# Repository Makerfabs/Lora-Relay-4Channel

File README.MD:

Lora-Relay-4Channel
 ==
Introduce
-
4-Channel Lora Relay-10A based on the Arduino, users can program it with Arduino IDE, which is very easy especially suit for the none-programmers. There are also guide for users to learn how to create the first IoT project with this board, with which the starters can learn the hardware and programming skill quickly. <br>
[Makerfabs Wiki](https://makerfabs.com/wiki/index.php?title=Main_Page) <br>
<br/>

Feature
-
* ATMEL Atmega328P: High Performance, Low Power Atmel®AVR® 8-Bit Microcontroller
* Speed Grade:20Mhz
* Flash:32Kbytes
* RAM: 2KBytes
* EEPROM: 1Kbytes
* Relay type: General Purpose 
* Rated current of relay contact: 10A
* Coil type of relay: Non Latching
* Coil voltage of relay: 5V
* Switching voltage of relay: (277VAC , 28VDC) Max
* DC12V or 5V input

Usage
-
 ### Hardware connection
The USB TO UART TOOL is needed to connect the module and PC. <br>
The pins connections is: 
|4-Channel Lora Relay-10A |USB-to-UART Tool |
|---|---|
|3V3 |3V3 |
|GND |GND |
|RX |TXD |
|TX |RXD |

 ### Software setup
Open the Arduino, select the tools menu and set the parameter, as the figure:<br>

 ### Lora Transmitter
Prepare a Lora receiver and put it aside.<br>
Open the code "LoraTransmitter/LoraTransmitter.ino" and modify the frequency macro according to your board is 433Mhz or 868Mhz or 915Mhz. <br>
```
#define RF95_FREQ 868.0  
```
Verify and upload it. <br>
  <br>
Open the “Tools—Serial Monitor” and the information of Lora Transmitter will be shown in the monitor, as the picture. 

 ### Lora receiver
Open the "LoraReceiver/LoraReceiver.ino" and modify the frequency macro according to your board is 433Mhz or 868Mhz or 915Mhz. 
```
#define RF95_FREQ 868.0 
```
Verify and upload it. After finish, open the “Tools—Serial Monitor”, If have a transmitter next to it, the receive will receive data sent by the Transmitter and the monitor will show the received information in the window, as the picture.
  <br>
If the receiver has received it, the relay will be turned on or turned off. Light on when COM connect to NO, light off when COM connect to NC and Normally light off.<br>
 <br>
Control relay pins: <br>
|Atmega328P	|Relay |
|---|---|
|D4	|K1 |
|D3	|K2 |
|A3	|K3 |
|A2	|K4 |

The following table lists all of the relay's pins and their functionality.<br>
|Pin	|Description | 
|---|---|
|NC	Normally |Closed | 
|NO	Normally |Opened | 
|COM	|Switch Common |

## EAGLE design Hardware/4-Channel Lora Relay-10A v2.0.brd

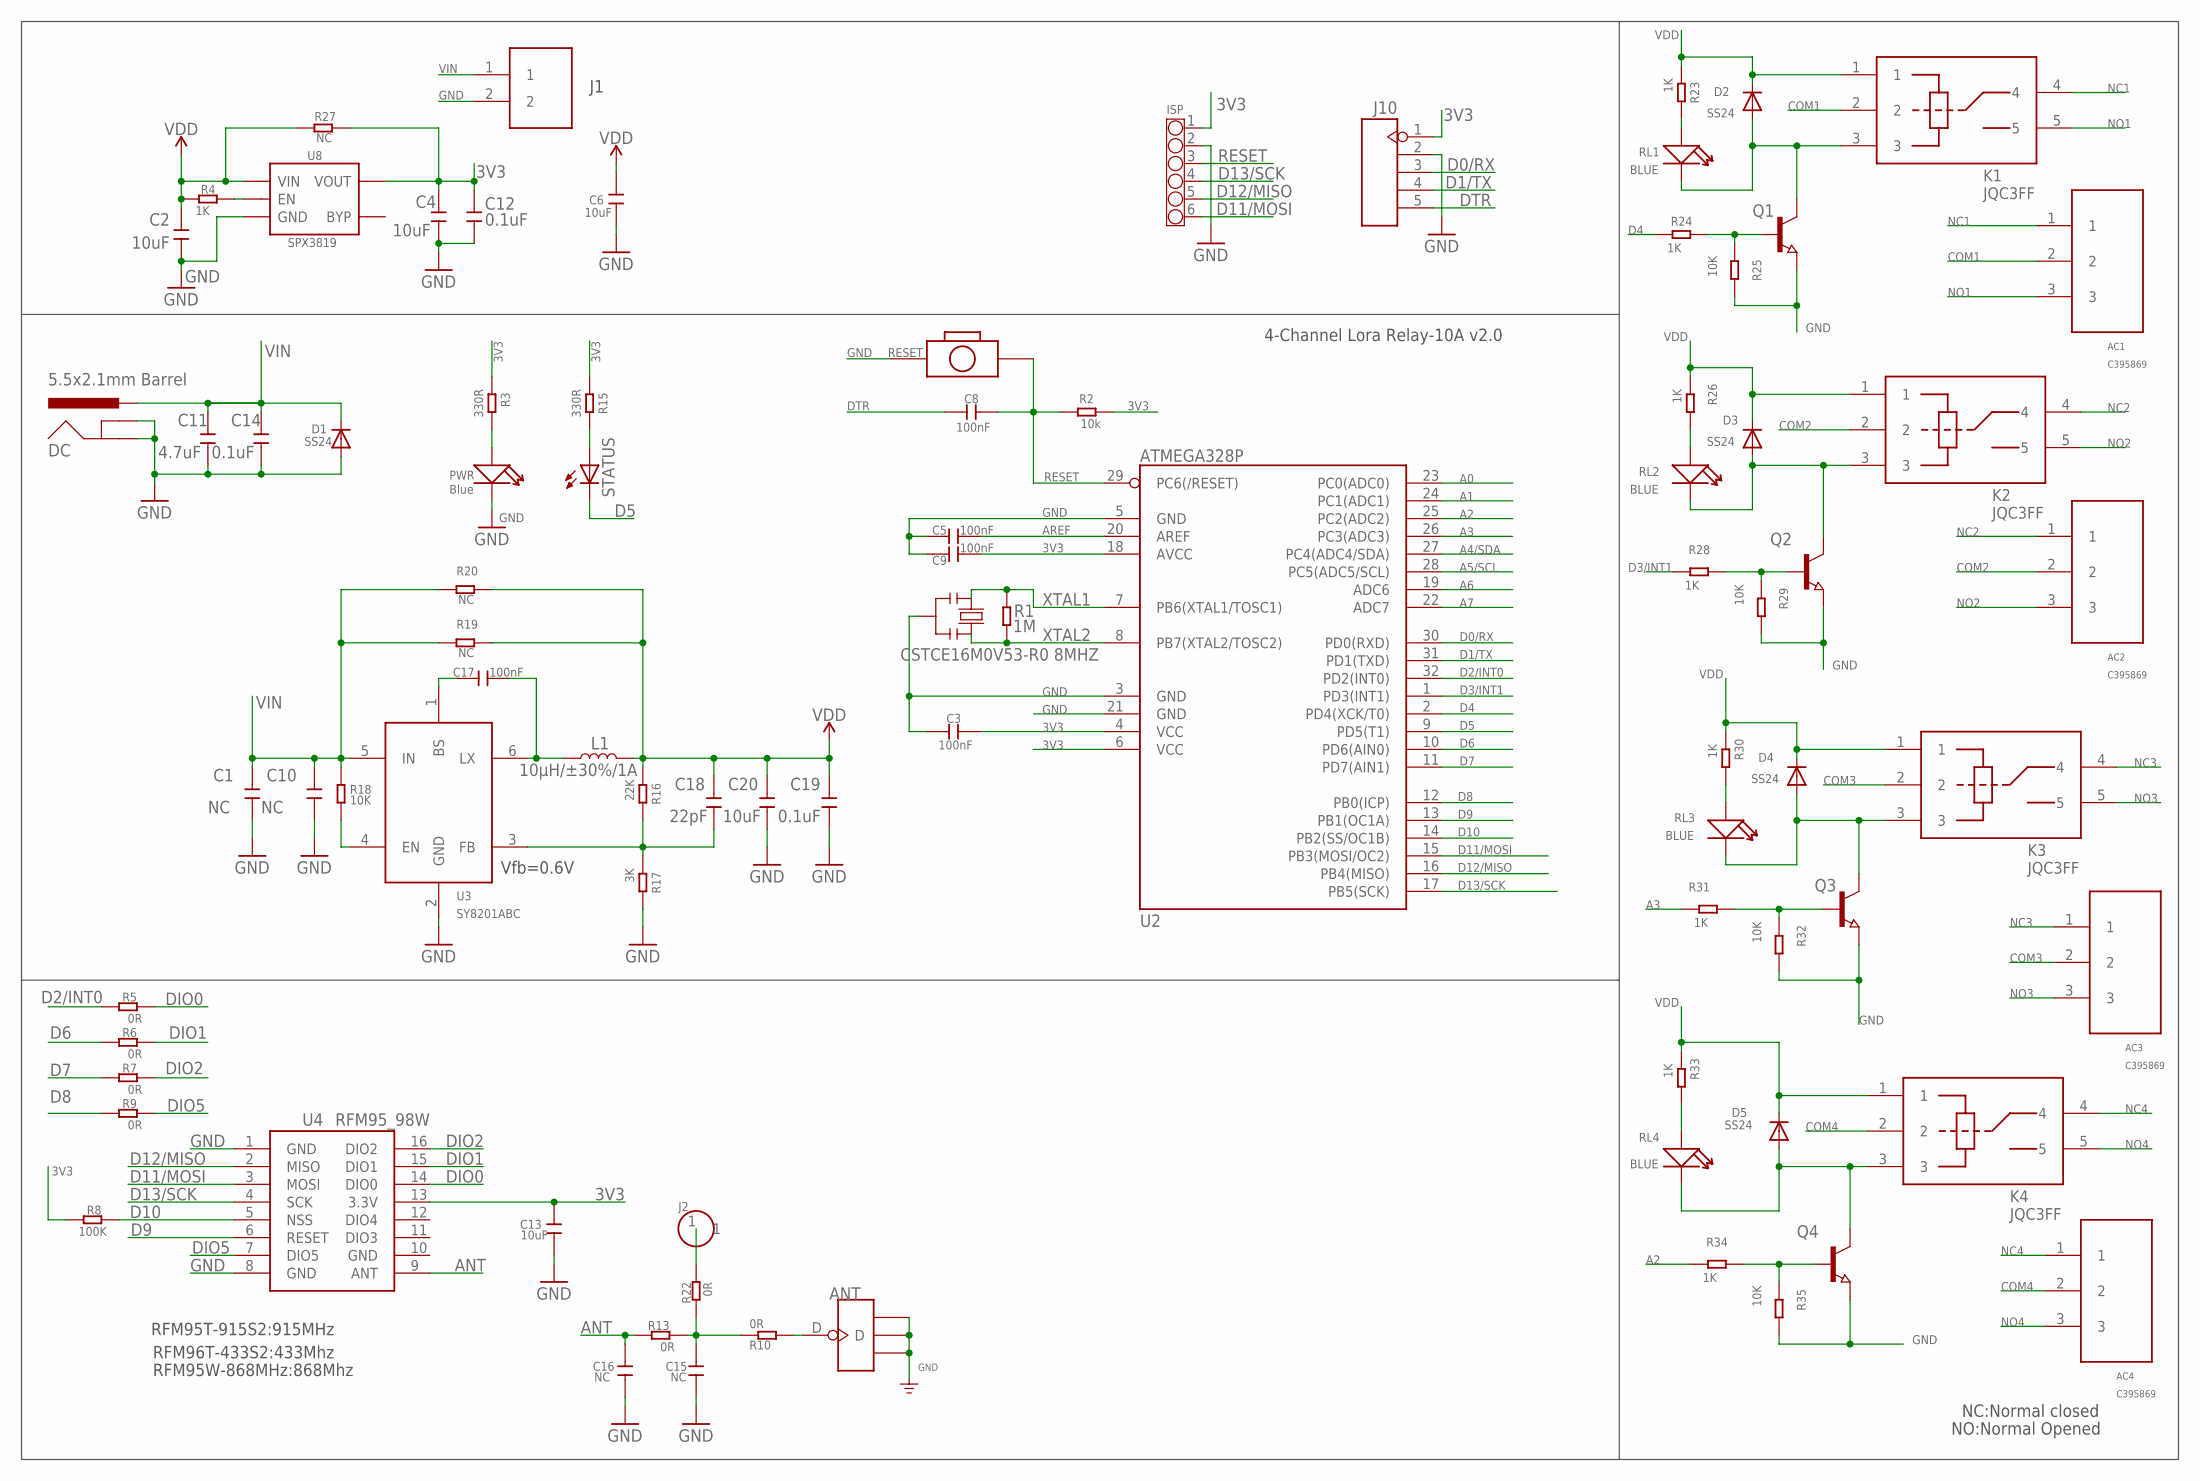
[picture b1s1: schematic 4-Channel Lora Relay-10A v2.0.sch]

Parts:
AC1, AC2, AC3, AC4: C395869; PIN_3P
ANT: ANTENNA-U-FL; 4P-U-FL
C1, C10, C15, C16: NC; 0603
C2, C4, C6, C13, C20: 10uF; 0603
C3, C5, C8, C9, C17: 100nF; 0603
C11: 4.7uF; 0603
C12, C14, C19: 0.1uF; 0603
C18: 22pF; 0603
D1, D2, D3, D4, D5: SS24; SMADIODE
DC: 5.5x2.1mm Barrel; POWER_JACK_SMD
ISP: CONNECTOR-HEADER-6P-3460270P1; 1X6P-2.54-8.5-BLACK-FEMALE
J1: PH2.0-2P-90-DIP
J2: HEADER-1P-50; 1P-100/50MIL
J10: HEADER-5P-2.54; 5P-2.54
K1, K2, K3, K4: JQC3FF; DIP5_JQC3FF
L1: 10µH/±30%/1A; CR54
PWR: Blue; LED-0603
Q1, Q2, Q3, Q4: NPN-TRANSISTOR_SOT23; SOT23
R1: 1M; R0603
R2: 10k; R0603
R3, R15: 330R; R0603
R4, R23, R24, R26, R28, R30, R31, R33, R34: 1K; R0603
R5, R6, R7, R9, R10, R13, R22: 0R; R0603
R8: 100K; R0603
R16: 22K; R0603
R17: 3K; R0603
R18, R25, R29, R32, R35: 10K; R0603
R19, R20, R27: NC; R0603
RESET: BOTTON-2P-90D; 2P-7.62X3.56-90D
RL1, RL2, RL3, RL4: BLUE; LED-0603
STATUS: LED5MM
U2: ATMEGA328P; TQFP32
U3: SY8201ABC; SOT-23-6
U4: RFM95_98W; RFM92_93W
U8: SPX3819; SOT23-5
Y1: CSTCE16M0V53-R0 8MHZ; RESONATOR

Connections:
3V3: C3.2, C4.2, C9.2, C12.2, C13.2, ISP.1, J10.1, R2.1, R3.1, R8.2, R15.1, R27.2, U2.4 (VCC), U2.6 (VCC), U2.18 (AVCC), U4.13 (3.3V), U8.5 (VOUT)
A0: U2.23 (PC0(ADC0))
A1: U2.24 (PC1(ADC1))
A2: R34.1, U2.25 (PC2(ADC2))
A3: R31.1, U2.26 (PC3(ADC3))
A4/SDA: U2.27 (PC4(ADC4/SDA))
A5/SCL: U2.28 (PC5(ADC5/SCL))
A6: U2.19 (ADC6)
A7: U2.22 (ADC7)
ANT: C16.2, R13.2, U4.9 (ANT)
AREF: C5.2, U2.20 (AREF)
COM1: AC1.2, K1.2
COM2: AC2.2, K2.2
COM3: AC3.2, K3.2
COM4: AC4.2, K4.2
D0/RX: J10.3, U2.30 (PD0(RXD))
D1/TX: J10.4, U2.31 (PD1(TXD))
D2/INT0: R5.1, U2.32 (PD2(INT0))
D3/INT1: R28.1, U2.1 (PD3(INT1))
D4: R24.1, U2.2 (PD4(XCK/T0))
D5: STATUS.K (C), U2.9 (PD5(T1))
D6: R6.1, U2.10 (PD6(AIN0))
D7: R7.1, U2.11 (PD7(AIN1))
D8: R9.1, U2.12 (PB0(ICP))
D9: U2.13 (PB1(OC1A)), U4.6 (RESET)
D10: R8.1, U2.14 (PB2(SS/OC1B)), U4.5 (NSS)
D11/MOSI: ISP.6, U2.15 (PB3(MOSI/OC2)), U4.3 (MOSI)
D12/MISO: ISP.5, U2.16 (PB4(MISO)), U4.2 (MISO)
D13/SCK: ISP.4, U2.17 (PB5(SCK)), U4.4 (SCK)
DIO0: R5.2, U4.14 (DIO0)
DIO1: R6.2, U4.15 (DIO1)
DIO2: R7.2, U4.16 (DIO2)
DIO5: R9.2, U4.7 (DIO5)
DTR: C8.1, J10.5
GND: ANT.GND1, ANT.GND2, ANT.GND3, C1.1, C2.1, C3.1, C4.1, C5.1, C6.1, C9.1, C10.1, C11.1, C12.1, C13.1, C14.1, C15.1, C16.1, C19.1, C20.1, D1.A, DC.GND (GNDBREAK), DC.P$4 (GND), ISP.2, J1.2, J10.2, PWR.-, Q1.2 (E), Q2.2 (E), Q3.2 (E), Q4.2 (E), R17.2, R25.2, R29.2, R32.2, R35.2, RESET.P$1 (1), U2.3 (GND), U2.5 (GND), U2.21 (GND), U3.2 (GND), U4.1 (GND), U4.8 (GND), U4.10 (GND), U8.2 (GND), Y1.2
unnamed: ANT.D, R10.2
unnamed: R23.2, RL1.+
unnamed: C15.2, R10.1, R13.1, R22.2
unnamed: R15.2, STATUS.A
unnamed: C17.2, L1.P$1 (1), U3.6 (LX)
unnamed: PWR.+, R3.2
unnamed: C17.1, U3.1 (BS)
unnamed: D2.A, K1.3, Q1.3 (C), RL1.-
unnamed: C18.1, R16.2, R17.1, U3.3 (FB)
unnamed: R18.2, U3.4 (EN)
unnamed: J2.1, R22.1
unnamed: Q1.1 (B), R24.2, R25.1
unnamed: R26.2, RL2.+
unnamed: D3.A, K2.3, Q2.3 (C), RL2.-
unnamed: Q2.1 (B), R28.2, R29.1
unnamed: R4.2, U8.3 (EN)
unnamed: R30.2, RL3.+
unnamed: D4.A, K3.3, Q3.3 (C), RL3.-
unnamed: Q3.1 (B), R31.2, R32.1
unnamed: R33.2, RL4.+
unnamed: D5.A, K4.3, Q4.3 (C), RL4.-
unnamed: Q4.1 (B), R34.2, R35.1
NC1: AC1.1, K1.4
NC2: AC2.1, K2.4
NC3: AC3.1, K3.4
NC4: AC4.1, K4.4
NO1: AC1.3, K1.5
NO2: AC2.3, K2.5
NO3: AC3.3, K3.5
NO4: AC4.3, K4.5
RESET: C8.2, ISP.3, R2.2, RESET.P$2 (2), U2.29 (PC6(/RESET))
VDD: C2.2, C6.2, C18.2, C19.2, C20.2, D2.C, D3.C, D4.C, D5.C, K1.1, K2.1, K3.1, K4.1, L1.P$2 (2), R4.1, R16.1, R19.2, R20.2, R23.1, R26.1, R27.1, R30.1, R33.1, U8.1 (VIN)
VIN: C1.2, C10.2, C11.2, C14.2, D1.C, DC.VIN0 (PWR), J1.1, R18.1, R19.1, R20.1, U3.5 (IN)
XTAL1: R1.2, U2.7 (PB6(XTAL1/TOSC1)), Y1.1
XTAL2: R1.1, U2.8 (PB7(XTAL2/TOSC2)), Y1.3

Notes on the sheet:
RFM95T-915S2:915MHz
RFM96T-433S2:433Mhz
RFM95W-868MHz:868Mhz
NC:Normal closed
NO:Normal Opened
4-Channel Lora Relay-10A v2.0
Vfb=0.6V

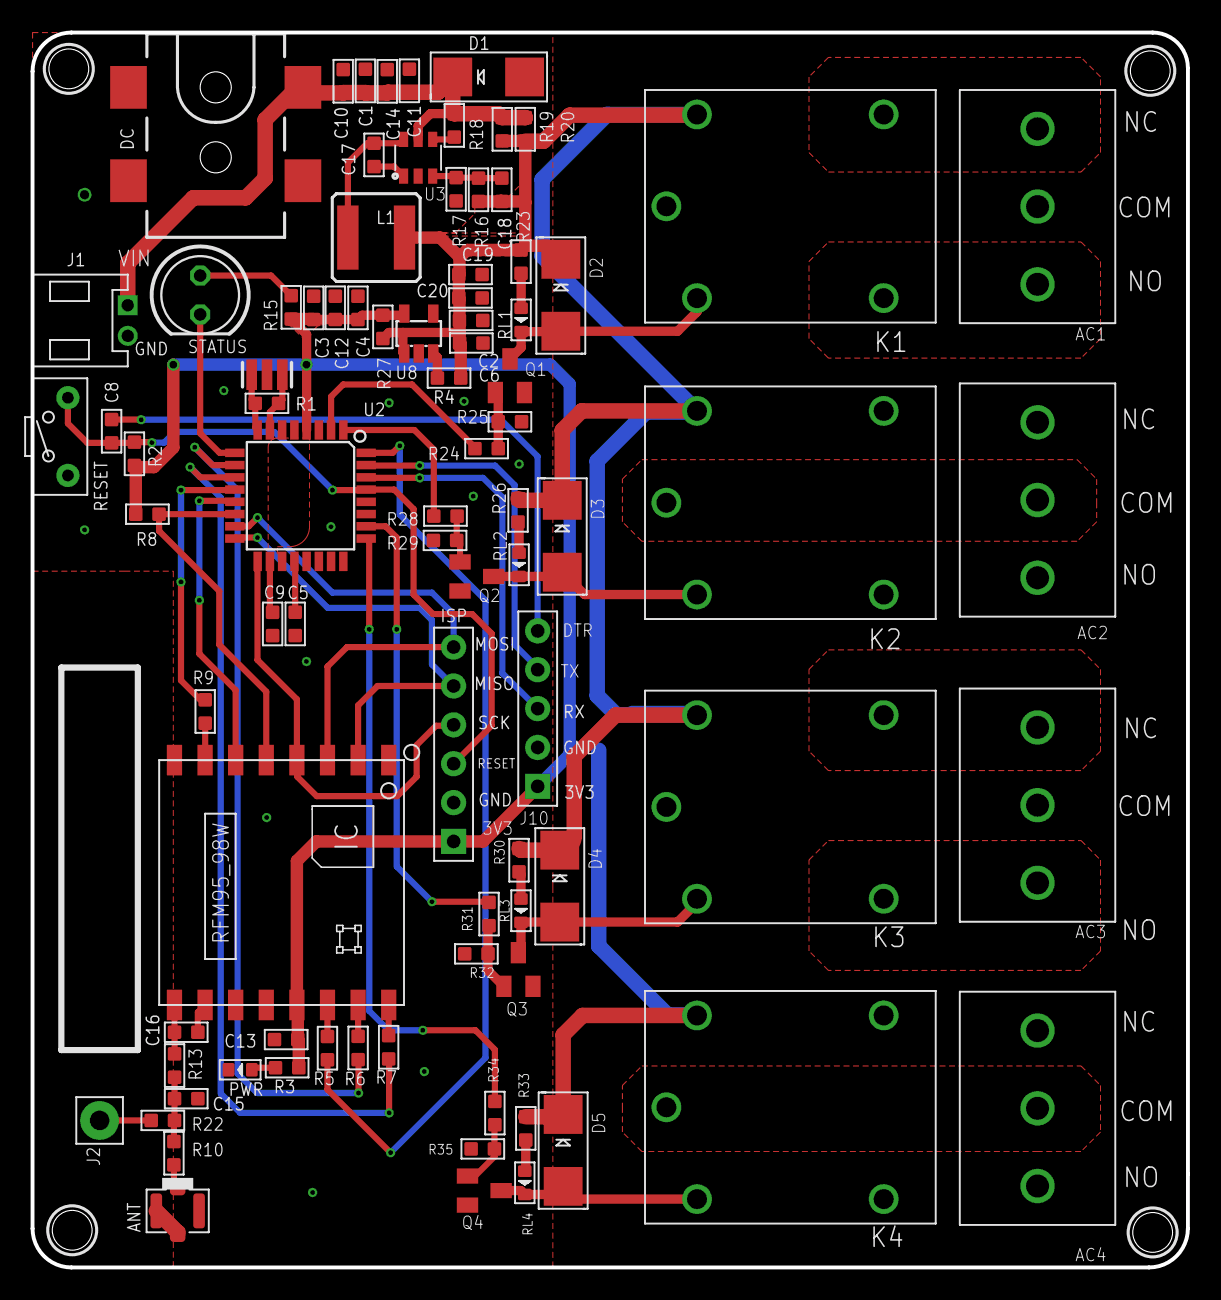
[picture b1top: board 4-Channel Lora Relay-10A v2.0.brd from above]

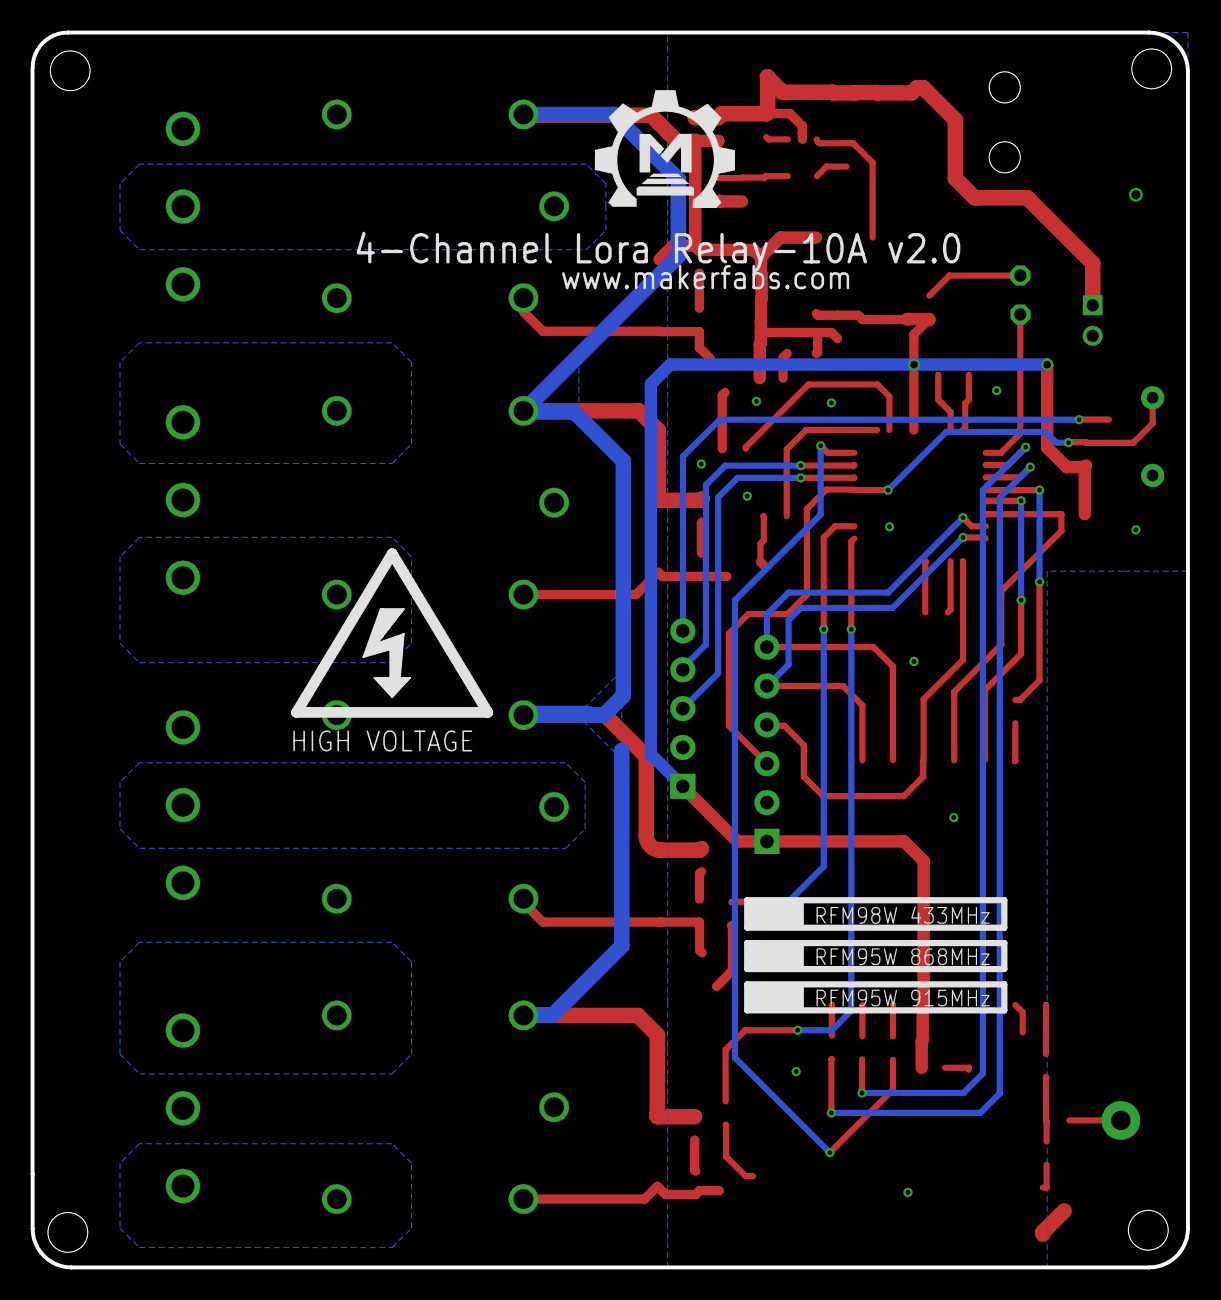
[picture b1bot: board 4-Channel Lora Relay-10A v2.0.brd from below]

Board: 2 copper layers, 75.5 x 80.7 mm, 88 parts (2 on the bottom side), 64 nets.

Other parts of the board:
U$1: MAKERFABS_0.3
U$3: HIGH-VOLTAGE-1.5

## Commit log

2020-09-22 0922
2020-09-22 0001
2020-09-22 0002
2020-09-22 0004
2020-09-22 0005
2020-09-22 0006
2020-09-22 Hardware
2020-09-22 3pic
2020-09-22 1pic
2020-11-10 rename
2020-11-27 create
2020-11-27 file
2020-11-27 delete
2020-12-31 add files

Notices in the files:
parts and their libraries:
SparkFun-Connectors: Licensing: Creative Commons ShareAlike 4.0 International - https://creativecommons.org/licenses/by-sa/4.0
